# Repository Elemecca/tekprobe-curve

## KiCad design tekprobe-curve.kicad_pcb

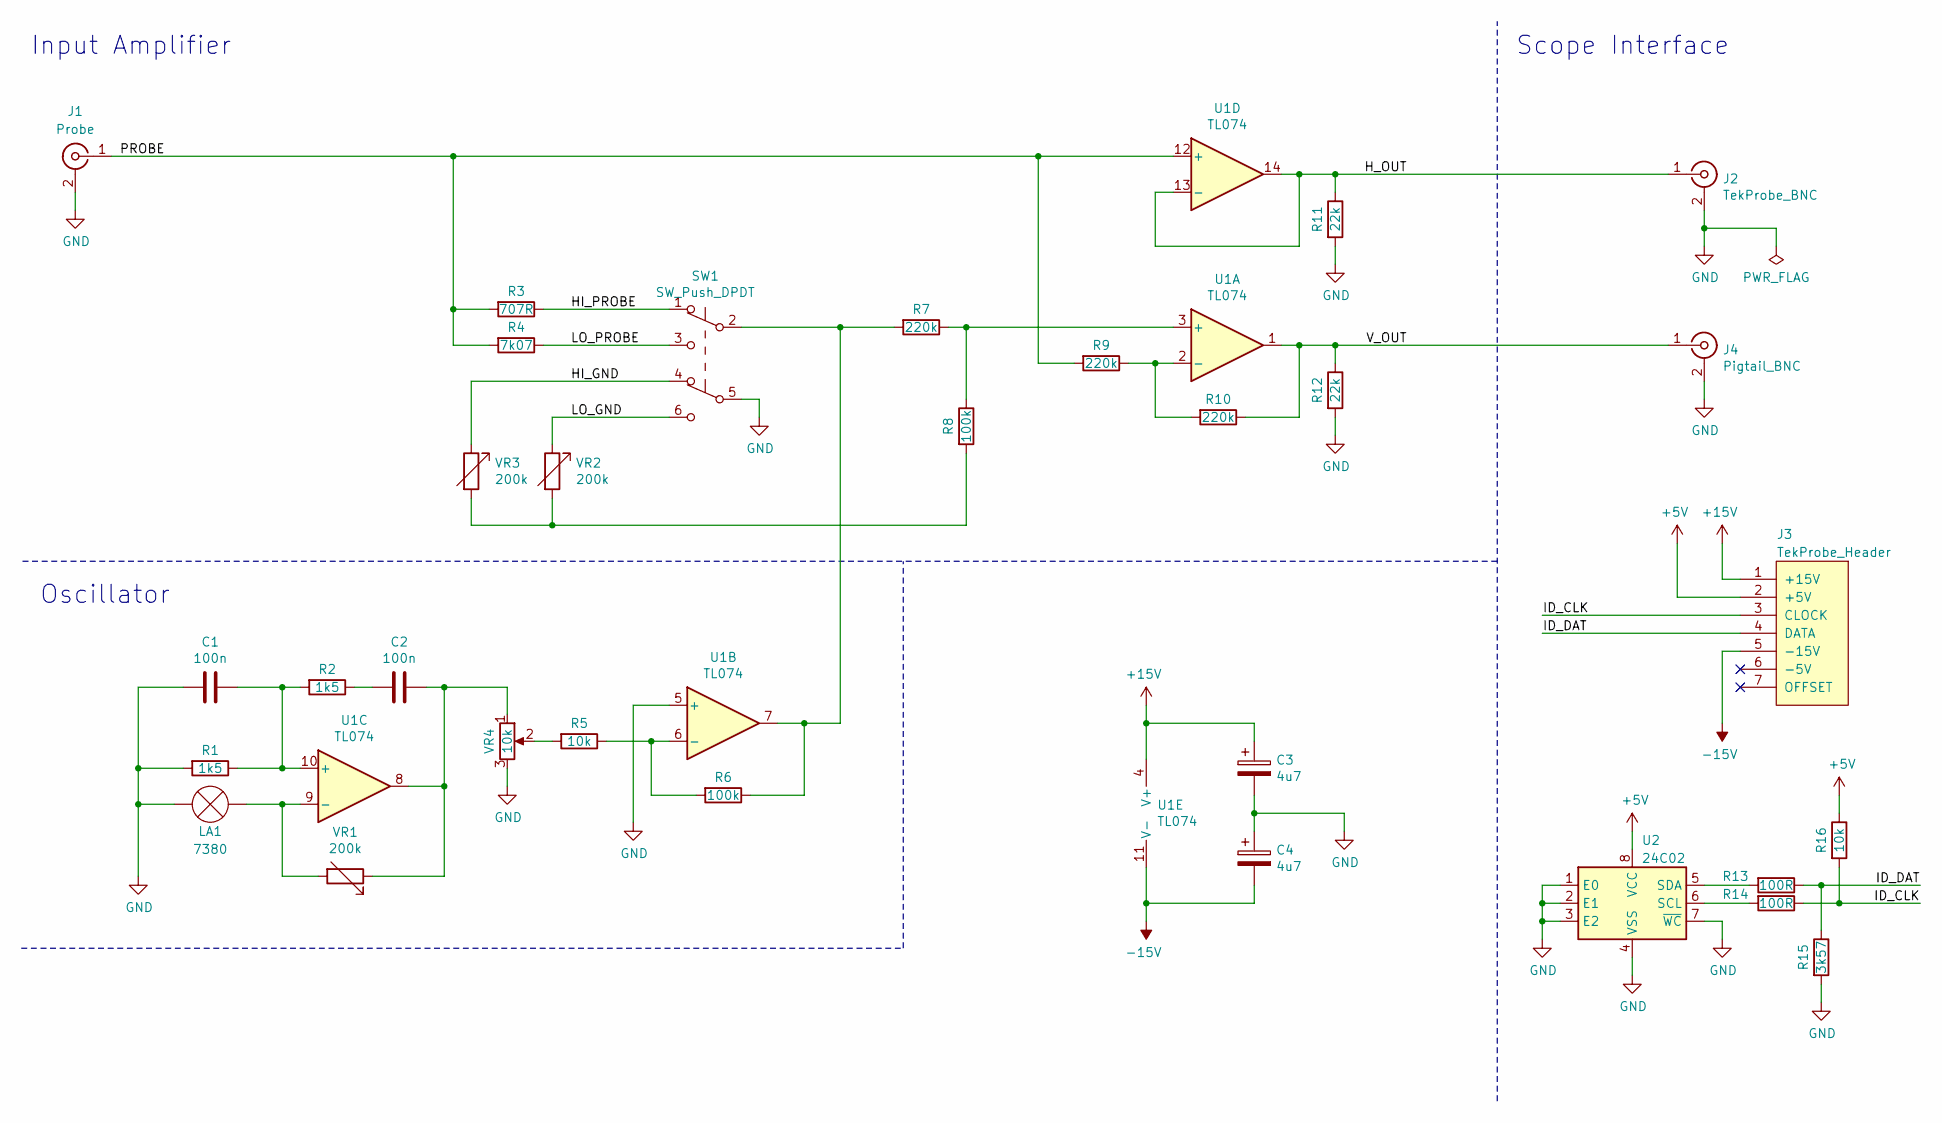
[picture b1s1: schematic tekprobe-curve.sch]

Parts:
C1, C2: 100n; C_0402_1005Metric
C3, C4: 4u7; C_1206_3216Metric
J1: Probe; U.FL_Hirose_U.FL-R-SMT-1_Vertical
J2: TekProbe_BNC; U.FL_Hirose_U.FL-R-SMT-1_Vertical
J3: TekProbe_Header; PinHeader_1x07_P1.27mm_Vertical
J4: Pigtail_BNC; U.FL_Hirose_U.FL-R-SMT-1_Vertical
LA1: 7380
R1, R2: 1k5; R_0402_1005Metric
R3: 707R; R_0402_1005Metric
R4: 7k07; R_0402_1005Metric
R5, R16: 10k; R_0402_1005Metric
R6, R8: 100k; R_0402_1005Metric
R7, R9, R10: 220k; R_0402_1005Metric
R11, R12: 22k; R_0402_1005Metric
R13, R14: 100R; R_0402_1005Metric
R15: 3k57; R_0402_1005Metric
SW1: SW_Push_DPDT
U1: TL074; SOIC-14_3.9x8.7mm_P1.27mm
U2: 24C02; SOIC-8_3.9x4.9mm_P1.27mm
VR1, VR2, VR3: 200k; Potentiometer_Bourns_TC33X_Vertical
VR4: 10k; Potentiometer_Bourns_TC33X_Vertical

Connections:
+5V: J3.2 (+5V), R16.1, U2.8 (VCC)
+15V: C3.1, J3.1 (+15V), U1.4 (V+)
-15V: C4.2, J3.5 (-15V), U1.11 (V-)
/HI_GND: SW1.4 (A), VR3.1
/HI_PROBE: R3.1, SW1.1 (A)
/H_OUT: J2.1 (In), R11.1, U1.13 (-), U1.14
/ID_CLK: J3.3 (CLOCK), R14.1, R16.2
/ID_DAT: J3.4 (DATA), R13.1, R15.1
/LO_GND: SW1.6 (C), VR2.1
/LO_PROBE: R4.1, SW1.3 (C)
/PROBE: J1.1 (In), R3.2, R4.2, R9.2, U1.12 (+)
/V_OUT: J4.1 (In), R10.1, R12.1, U1.1
GND: C1.2, C3.2, C4.1, J1.2 (Ext), J2.2 (Ext), J4.2 (Ext), LA1.1 (-), R1.2, R11.2, R12.2, R15.2, SW1.5 (B), U1.5 (+), U2.1 (E0), U2.2 (E1), U2.3 (E2), U2.4 (VSS), U2.7 (~WC), VR4.3
unnamed: C1.1, R1.1, R2.2, U1.10 (+)
unnamed: C2.1, U1.8, VR1.1, VR4.1
unnamed: C2.2, R2.1
unnamed: LA1.2 (+), U1.9 (-), VR1.2
unnamed: R5.1, R6.2, U1.6 (-)
unnamed: R5.2, VR4.2
unnamed: R6.1, R7.2, SW1.2 (B), U1.7
unnamed: R7.1, R8.1, U1.3 (+)
unnamed: R8.2, VR2.2, VR3.2
unnamed: R9.1, R10.2, U1.2 (-)
unnamed: R13.2, U2.5 (SDA)
unnamed: R14.2, U2.6 (SCL)

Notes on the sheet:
Scope Interface
Input Amplifier
Oscillator

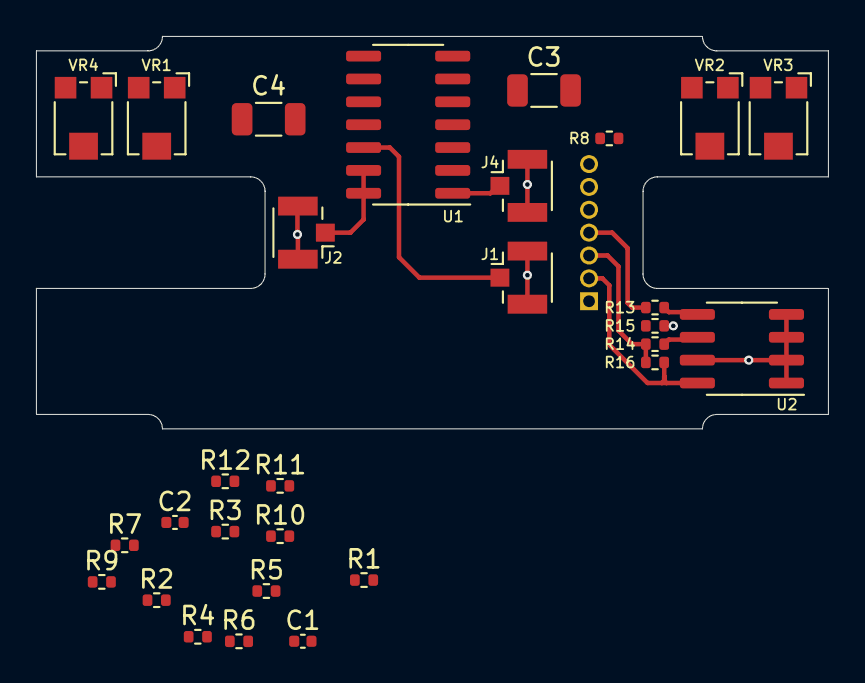
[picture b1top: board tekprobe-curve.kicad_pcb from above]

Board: 4 copper layers, 44.0 x 21.8 mm, 30 parts (1 on the bottom side), 21 nets.

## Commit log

2022-03-06 Start from Carlson's schematic.
2022-03-09 Convert to KiCad 6.
2022-03-09 Move board into directory.
2022-03-10 Start work on TekProbe ring footprint.
2022-03-10 Add remaining pads to TekProbe_Ring.
2022-03-10 Add links between data pads in TekProbe_Ring.
2022-03-10 Add silkscreen outline to TekProbe_Ring.
2022-03-10 Add global parameters to TekProbe_Ring.
